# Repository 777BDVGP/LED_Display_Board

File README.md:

# LED Display Board

A WiFi LED-matrix clock for the house: it shows the time and scrolls
**birthdays, anniversaries and reminders** on the day, with a buzzer, an
optional radar sensor that wakes the display when someone is in the room, and
phone notifications through [ntfy](https://ntfy.sh). Everything is set up from
its own web pages on your WiFi — no cloud, no app.

Several clocks in one house keep each other in sync: add or change a reminder
on one clock and the others get it within seconds.

**Install page, pictures and updates:** https://777bdvgp.github.io/LED_Display_Board/

**How to use it — every page and setting:** [USER_GUIDE.md](USER_GUIDE.md)
· **How to build it:** [Build_Files/README.md](Build_Files/README.md)

> **Time zone:** Greenwich (GMT) out of the box — choose yours on
> SETTINGS → TIME ZONE (daylight saving switches by itself).

## Features

- **Clock** on a WS2812 (NeoPixel) LED matrix, time from the internet (NTP)
  in your own time zone (SETTINGS, 26 zones, daylight saving automatic),
  brightness from a light sensor (LDR), display wakes on the radar sensor.
- **Birthdays & anniversaries** — shown on the day, with age.
- **Reminders** — once, daily, weekly, first/last weekday of the month or of
  one month a year; colour, buzzer pattern, repeat count, ntfy push.
  - **Valid Periods** — named sets of date ranges (e.g. school terms); a
    reminder can be limited to fire only inside them.
  - Grouped list (Daily / Weekly / Monthly / Yearly / Once / Expired) with search.
- **Quick reminder** — "remind me in 40 minutes" in two taps.
- **Exercises** — guided exercise programmes counted out on the display.
- **Multi-clock sync** — up to 4 clocks share birthdays, anniversaries,
  reminders and valid periods.
- **Backups** — CSV export / import of every list (Disk Tools).
- **Updates**: ABOUT → CHECK FOR UPDATE / INSTALL FROM GITHUB, or
  UPLOAD & INSTALL a `.bin` from the browser.

## WiFi setup

1. Install the firmware (see *Installing the firmware* below).
2. The clock opens the WiFi hotspot **LEDClock-Setup**. Connect a phone to it —
   the setup page opens by itself (otherwise browse to `http://192.168.4.1/`).
   Pick your network, type the password, choose a **fixed IP** (recommended)
   or **Automatic (DHCP)**, press **SAVE & RESTART**.
3. Put the phone back on your normal WiFi and open `http://<the clock's IP>/`.

**More networks:** OTHER → **WIFI NETWORKS** lists the saved networks (the
passwords are never shown) with **DELETE**, and **ADD NETWORK** for another
one. At start-up the clock tries the saved networks in range, strongest first.
If none can be reached for a few minutes, the **LEDClock-Setup** hotspot opens
for 5 minutes so you can add a network from a phone, then the clock restarts
and tries again.

## Hardware — build it yourself

*The finished clock, with an optional picture frame around the acrylic box.*

Everything to build the clock is in [`Build_Files/`](Build_Files) — see its
**[build guide](Build_Files/README.md)**:

- STL files to 3D-print (corner mounts, PCB / power-supply / wire supports,
  radar + button + light-sensor holder),
- DXF files to laser-cut from 3 mm acrylic (front window, LED backplate, top,
  bottom, sides, back),
- `Build_Files/PCB/` — Eagle schematic + board (V14) and the Gerber ZIP to
  order the board (takes an **ESP32-DevKitC-32E** or a **WEMOS D1 Mini ESP32** —
  either one works),
- `SparesList.xlsx` — every part with where to buy it.

> **Which ESP32?** Use the original **ESP32-DevKitC-32E** from Espressif (the
> prototype's came from Espressif's own store on AliExpress). A single clock
> worked fine on a WEMOS D1 Mini ESP32, but with three clocks syncing in the
> background the WiFi traffic disturbed the LED display on the WEMOS; the
> DevKitC-32E runs clean.

The clock is powered from 230 V mains through a small enclosed power supply —
have the mains wiring done or checked by a qualified person.

## Pin map

| Part | GPIO | Notes |
|---|---|---|
| LED matrix data (WS2812) | 33 | |
| Buzzer (2N2222) | 17 | |
| Radar presence sensor | 23 | digital output, HIGH = presence |
| Terminate push-button | 27 | active HIGH |
| LDR (light sensor) | 35 | ADC1 |
| Status LED | 2 | on-board blue LED; fast blink = WiFi connecting / setup hotspot |

## Installing the firmware

No PlatformIO needed: open the [install page](https://777bdvgp.github.io/LED_Display_Board/)
in Chrome or Edge, plug the ESP32 in with a USB data cable, press **CONNECT**,
choose **Erase**, then **Install**.

## Building the firmware yourself

ESP-IDF 5.3 through PlatformIO:

```
cd LED_Display_Board
pio run -e esp32dev -t upload          # USB
```

Each build writes `firmware_out/LED_Display_Board_v<ver>.bin` (update — ABOUT
page UPLOAD & INSTALL) and `..._full.bin` (new board, flash at 0x0).

Optional built-in WiFi networks and default ntfy topics:
`src/wifi_secrets.example.h` (your copy `wifi_secrets.h` is never committed).

Publishing a new version (maintainer): `python sync_from_private.py`, build,
`python update_firmware.py "note"`, commit, push. After changing a DXF or STL
file: `python make_enclosure_zips.py` (rebuilds the two enclosure ZIPs).

## Licence

CC BY-NC 4.0 — see [LICENSE](LICENSE).

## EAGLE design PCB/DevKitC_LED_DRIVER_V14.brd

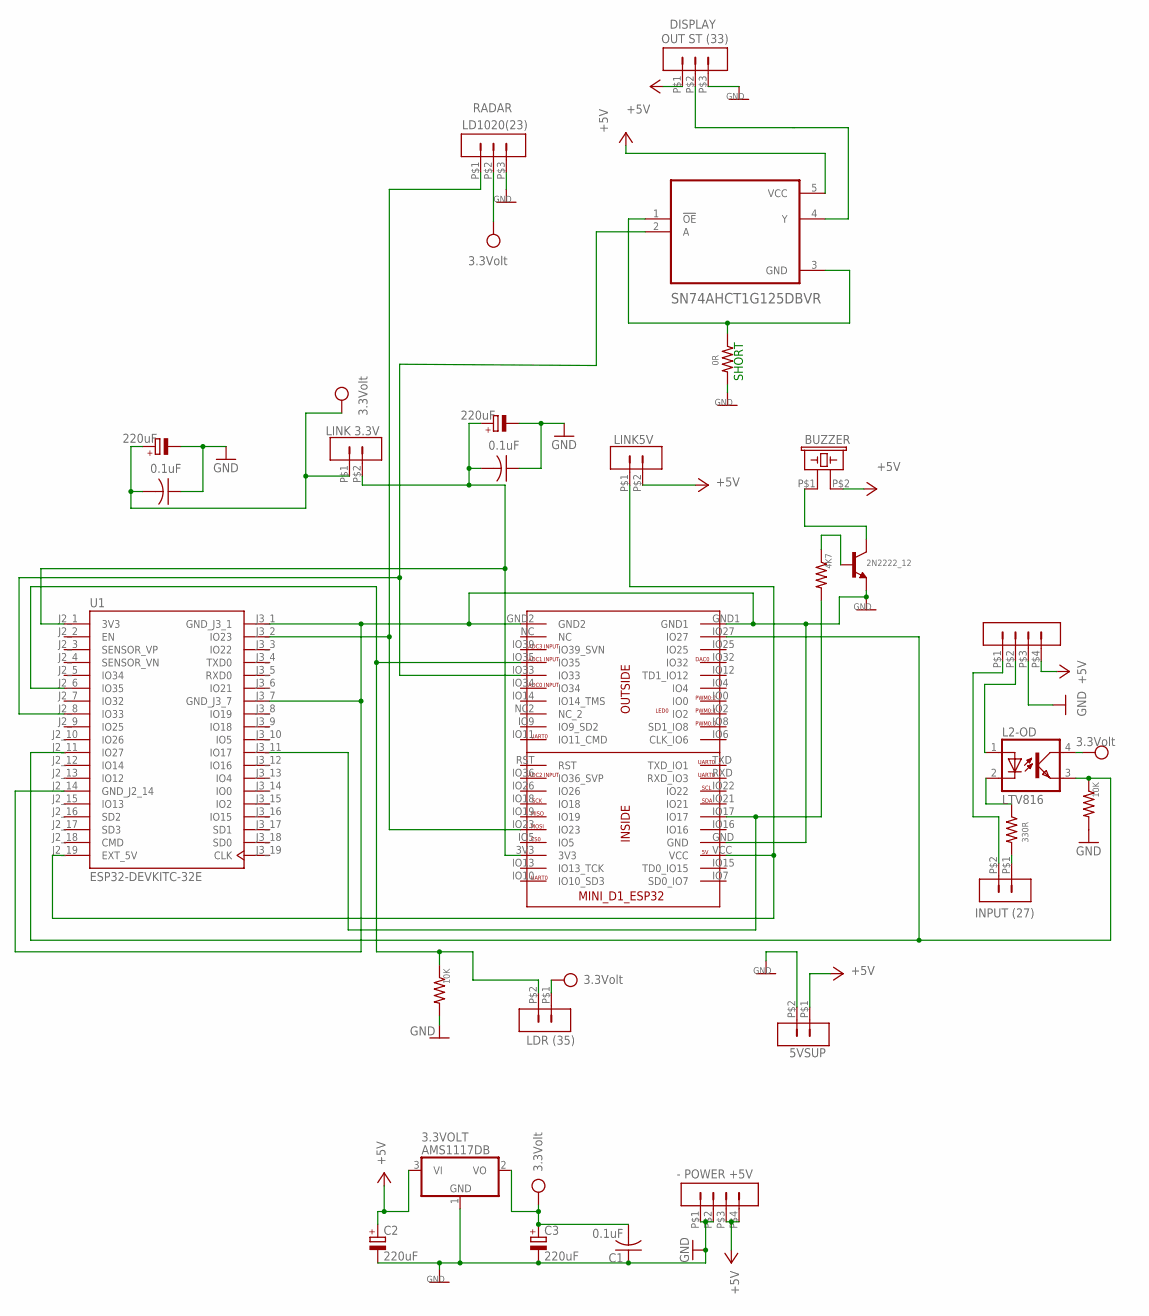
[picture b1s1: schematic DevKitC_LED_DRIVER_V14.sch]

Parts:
2N2222_12: 2N2222; TO92
3.3VOLT: AMS1117DB; SOT223
5VSUP: 5VSUP; 2WAYNORMAL
BUZZER: BUZZER (17); F/CM12P_2
C1, C4, C5: 0.1uF; C050-025X075
C2, C3, C6, C7: 220uF; E2,5-7
L2-OD: LTV816; DIL04
LD1020: LD1020(23); 3WAY_SH_NARROW
LINK3.3V: LDR (35); 2WAY_SH_NARROW
LINK5V: LINK5V; 2WAYNORMAL
OUT_DISPLAY: OUT ST (33); 3WAY_SH_NARROW
R3: 330R; R0805
R4, R7: 10K; R0805
R11: 0R; R0805
R48: 4K7; R0805
U1: ESP32-DEVKITC-32E; MODULE_ESP32-DEVKITC-32E
U4: SN74AHCT1G125DBVR; SOT95P280X145-5N
U$1: WEMOS_DI_MINI_ESP32_2; WEMOS_MINI_D1_ESP32_2
U$2: - POWER +5V; 4WAY_SH_NARROW
U$6: INPUT (27); 2WAY_SH_NARROW
U$15: LINK 3.3V; 2WAYNORMAL
U$18: 4WAYHEADERSTRIPJUMBER; 4WAY_JUMBER

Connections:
+5V: 3.3VOLT.3 (VI), 5VSUP.P$1 (1), BUZZER.P$2 (2), C2.+, LINK5V.P$2 (2), OUT_DISPLAY.P$1 (1), U4.5 (VCC), U$2.P$3 (3), U$2.P$4 (4), U$18.P$4 (4)
GND: 2N2222_12.3 (E), 3.3VOLT.1 (GND), 5VSUP.P$2 (2), C1.1, C2.-, C3.-, C4.1, C5.1, C6.-, C7.-, LD1020.P$3 (3), OUT_DISPLAY.P$3 (3), R4.2, R7.2, R11.2, U1.J2_14 (GND_J2_14), U1.J3_1 (GND_J3_1), U1.J3_7 (GND_J3_7), U$1.GND, U$1.GND1, U$1.GND2, U$2.P$1 (1), U$2.P$2 (2), U$18.P$3 (3)
unnamed: 2N2222_12.2 (B), R48.1
unnamed: R48.2, U1.J3_11 (IO17), U$1.IO17
unnamed: R3.2, U$6.P$1 (1)
unnamed: L2-OD.2 (C), R3.1
unnamed: U1.J2_8 (IO33), U4.2 (A), U$1.IO33
unnamed: OUT_DISPLAY.P$2 (2), U4.4 (Y)
unnamed: L2-OD.3 (EMIT), R7.1, U1.J2_11 (IO27), U$1.IO27
unnamed: LINK3.3V.P$2 (2), R4.1, U1.J2_6 (IO35), U$1.IO35
unnamed: C5.2, C6.+, U1.J2_1 (3V3), U$1.3V3, U$15.P$2 (2)
unnamed: 2N2222_12.1 (C), BUZZER.P$1 (1)
unnamed: R11.1, U4.1 (!OE), U4.3 (GND)
unnamed: U$6.P$2 (2), U$18.P$1 (1)
unnamed: LD1020.P$1 (1), U1.J3_2 (IO23), U$1.IO23
unnamed: L2-OD.1 (A), U$18.P$2 (2)
unnamed: LINK5V.P$1 (1), U1.J2_19 (EXT_5V), U$1.VCC
VCC: 3.3VOLT.2 (VO), C1.2, C3.+, C4.2, C7.+, L2-OD.4 (COL), LD1020.P$2 (2), LINK3.3V.P$1 (1), U$15.P$1 (1)

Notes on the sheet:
SHORT
RADAR
DISPLAY

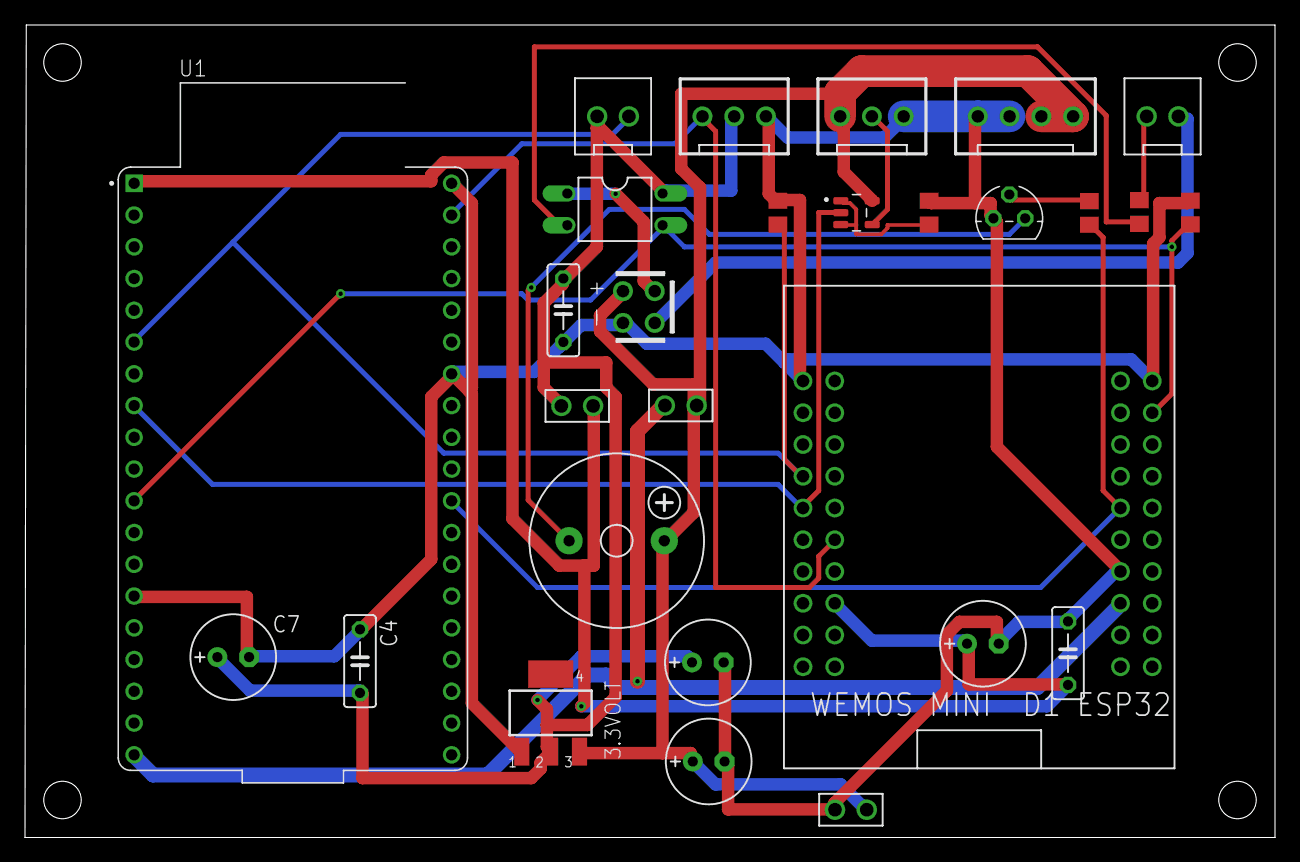
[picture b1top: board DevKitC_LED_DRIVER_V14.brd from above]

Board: 2 copper layers, 100.0 x 65.0 mm, 28 parts (0 on the bottom side), 18 nets.
